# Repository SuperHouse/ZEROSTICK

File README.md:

"ZeroStick" Zero-Deflection Assistive Technology Joystick
==========================================================

ZeroStick is a joystick that uses strain gauges to measure force
applied to it, without the joystick needing to move. The joystick
"position" is determined from the force being applied to it, instead of
any physical deflection of the stick.

The term "position" is used here to signify the virtual position of the
joystick, even though it doesn't physically move. As more force is
applied, the virtual position of the joystick is considered to change.

This allows it to be used by people with a limited range of motion,
such as from Duchenne muscular dystrophy.

The sensitivity of the joystick can be adjusted in software by changing
the scaling of the values detected by the strain gauges.

The position value is measured as % deflection from the zero (central)
position, ie: from -100% to +100%. This is equivalent to full effort by
the user in each direction.

The force applied to the load cells is measured using a NAU7802 ADC
with an I2C interface. The input channels are split so that a single
ADC can read both the X and the Y axis load cells sequentially.

You can view more details at:

  http://www.superhouse.tv/zerostick

Hardware
--------
The "Hardware" directory contains the PCB design as an EAGLE project.
EAGLE PCB design software is available from Autodesk free for
non-commercial use.

Firmware
--------
The "Firmware" directory contains example firmware as an Arduino
project.

The example firmware has three output methods:

1. Mouse output. When enabled and plugged into a computer, the ZeroStick
will emulate a USB mouse. Buttons on the ZeroStick can also send left
and right click events.

2. Joystick output. When enabled and plugged into a computer, the
ZeroStick will emulate a USB game controller with a joystick.

3. I2C digital potentiometer output. External I2C digital potentiometers
can be connected, which can then emulate a simple analog joystick
when connected to another device such as a wheelchair. This allows the
ZeroStick to control wheelchairs that expect to have a normal joystick
attached.

Credits
-------
  * Jonathan Oxer <jon@oxer.com.au>
  * Chris Fryer <chris.fryer78@gmail.com>

License
-------
Copyright 2019-2021 SuperHouse Automation Pty Ltd  www.superhouse.tv  

The hardware portion of this project is licensed under the TAPR Open
Hardware License (www.tapr.org/OHL). The "license" folder within this
repository contains a copy of this license in plain text format.

The software portion of this project is licensed under the Simplified
BSD License. The "licence" folder within this project contains a
copy of this license in plain text format.

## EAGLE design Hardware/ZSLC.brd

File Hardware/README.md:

SuperButton Assistive Technology Button
=======================================
Copyright 2020 SuperHouse Automation Pty Ltd <www.superhouse.tv>  
Designed by Jonathan Oxer

Load-cell based button that can have the required activation force
adjusted in software, to tune it based on the needs of the user.

Features:

 * 1 x input connection for a load-cell based button
 * 1 x USB connection for power or to emulate an input device
 * 1 x switched output (either N.O. or N.C.) to control other devices
 * 128x32 OLED to show current force reading and activation threshold
 * Rotary encoder to adjust activation threshold
 * "Tare" button to reset zero point
 * Pulse stretching feature controlled by slide switch

More information is available at:

  http://www.superhouse.tv/sb

INSTALLATION
------------
The design is saved as an EAGLE project. EAGLE PCB design software is
available from www.cadsoftusa.com free for non-commercial use. To use
this project download it and place the directory containing these files
into the "eagle" directory on your computer. Then open EAGLE and
navigate to the project.

DISTRIBUTION
------------
The specific terms of distribution of this project are governed by the
license referenced below.

LICENSE
-------
Licensed under the TAPR Open Hardware License (www.tapr.org/OHL).
The "license" folder within this repository also contains a copy of
this license in plain text format.

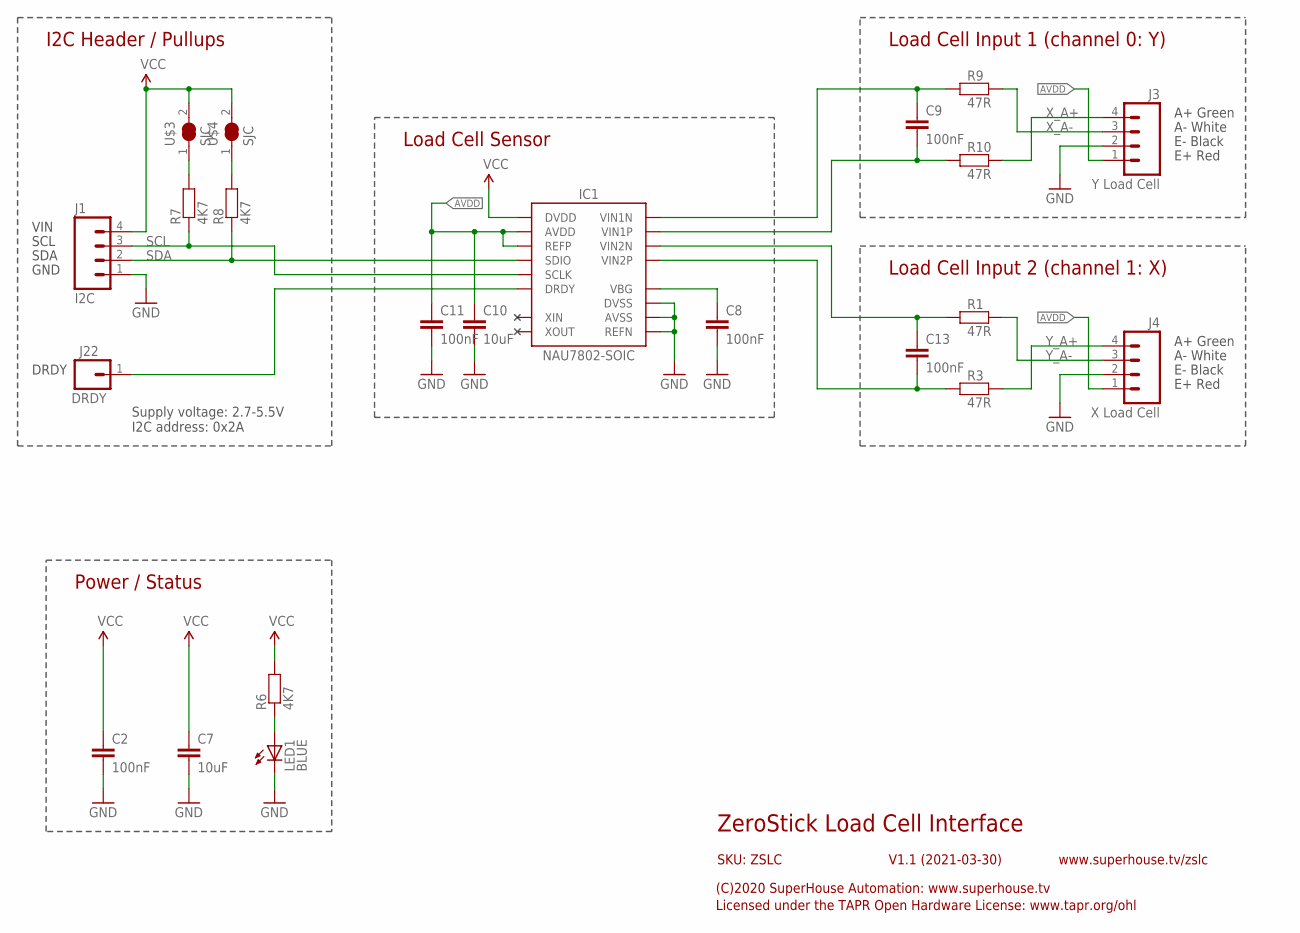
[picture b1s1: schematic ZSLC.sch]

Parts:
C2, C8, C9, C11, C13: 100nF; C0603
C7, C10: 10uF; C0805
IC1: NAU7802-SOIC; SO16
J1: I2C; 1X04
J3: Y Load Cell; 1X04-1.27-PLAIN
J4: X Load Cell; 1X04-1.27-PLAIN
J22: DRDY; 1X01
LED1: BLUE; LED-0603
R1, R3, R9, R10: 47R; R0603
R6, R7, R8: 4K7; R0603
U$3, U$4: SJC

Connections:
AVDD: C10.1, C11.1, IC1.1 (REFP), IC1.16 (AVDD), J3.1, J4.1
GND: C2.2, C7.2, C8.2, C10.2, C11.2, IC1.7 (REFN), IC1.8 (AVSS), IC1.9 (DVSS), J1.1, J3.2, J4.2, LED1.C
unnamed: IC1.12 (DRDY), J22.1
unnamed: C13.1, IC1.4 (VIN2N), R1.1
unnamed: C13.2, IC1.5 (VIN2P), R3.1
unnamed: LED1.A, R6.1
unnamed: C9.1, IC1.2 (VIN1N), R9.1
unnamed: C9.2, IC1.3 (VIN1P), R10.1
unnamed: C8.1, IC1.6 (VBG)
unnamed: R7.2, U$3.1
unnamed: R8.2, U$4.1
SCL: IC1.13 (SCLK), J1.3, R7.1
SDA: IC1.14 (SDIO), J1.2, R8.1
VCC: C2.1, C7.1, IC1.15 (DVDD), J1.4, R6.2, U$3.2, U$4.2
X_A+: J3.4, R10.2
X_A-: J3.3, R9.2
Y_A+: J4.4, R3.2
Y_A-: J4.3, R1.2

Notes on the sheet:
ZeroStick Load Cell Interface
V1.1 (2021-03-30)
SKU: ZSLC
(C)2020 SuperHouse Automation: www.superhouse.tv
Licensed under the TAPR Open Hardware License: www.tapr.org/ohl
www.superhouse.tv/zslc
Power / Status
Load Cell Input 1 (channel 0: Y)
Load Cell Input 2 (channel 1: X)
I2C Header / Pullups
E+ Red
E- Black
A- White
A+ Green
Supply voltage: 2.7-5.5V I2C address: 0x2A
Load Cell Sensor
VIN
SCL
SDA
GND
DRDY

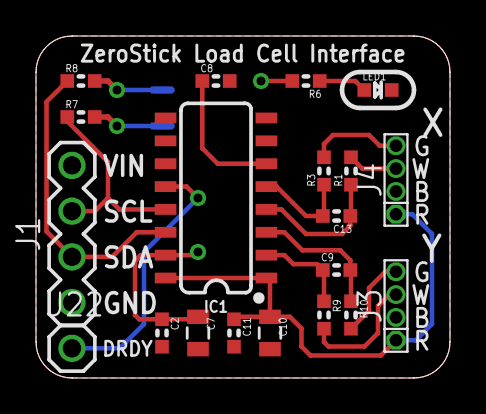
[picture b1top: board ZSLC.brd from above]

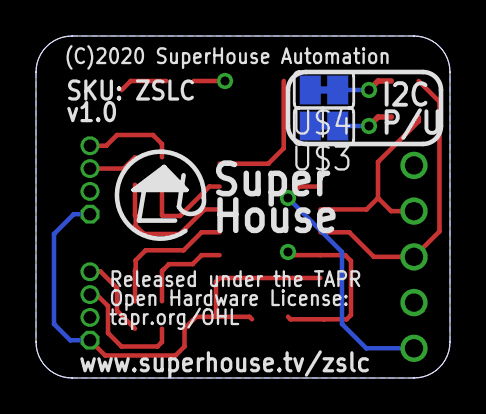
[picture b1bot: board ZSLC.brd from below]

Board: 2 copper layers, 23.0 x 19.0 mm, 22 parts (2 on the bottom side), 18 nets.

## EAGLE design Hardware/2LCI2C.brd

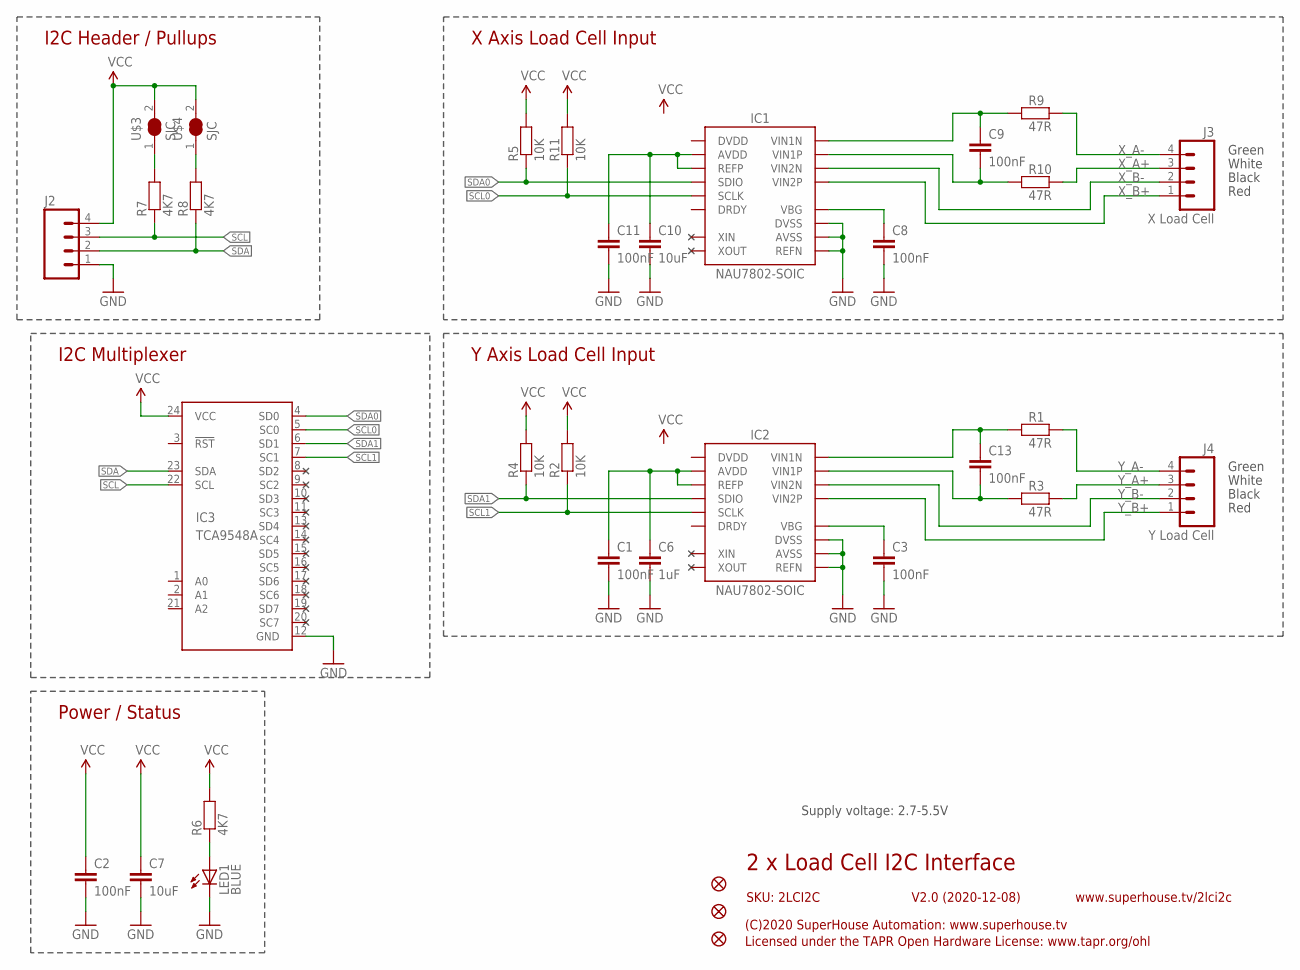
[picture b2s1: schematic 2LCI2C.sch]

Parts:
C1, C2, C3, C8, C9, C11, C13: 100nF; C0603
C6: 1uF; C0805
C7, C10: 10uF; C0805
IC1, IC2: NAU7802-SOIC; SO16
IC3: TCA9548A; TSSOP24
J2: M04-PLAIN; 1X04
J3: X Load Cell; 1X04-1.27-PLAIN
J4: Y Load Cell; 1X04-1.27-PLAIN
LED1: BLUE; LED-0603
R1, R3, R9, R10: 47R; R0603
R2, R4, R5, R11: 10K; R0603
R6, R7, R8: 4K7; R0603
U$3, U$4: SJC
U$5, U$10, U$11: FIDUCIAL1X2.5; FIDUCIAL-1X2.5

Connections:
GND: C1.2, C2.2, C3.2, C6.2, C7.2, C8.2, C10.2, C11.2, IC1.7 (REFN), IC1.8 (AVSS), IC1.9 (DVSS), IC2.7 (REFN), IC2.8 (AVSS), IC2.9 (DVSS), IC3.12 (GND), J2.1, LED1.C
unnamed: C3.1, IC2.6 (VBG)
unnamed: C13.1, IC2.2 (VIN1N), R1.1
unnamed: C1.1, C6.1, IC2.1 (REFP), IC2.16 (AVDD)
unnamed: C13.2, IC2.3 (VIN1P), R3.1
unnamed: LED1.A, R6.1
unnamed: C9.1, IC1.2 (VIN1N), R9.1
unnamed: C9.2, IC1.3 (VIN1P), R10.1
unnamed: C8.1, IC1.6 (VBG)
unnamed: C10.1, C11.1, IC1.1 (REFP), IC1.16 (AVDD)
unnamed: R7.2, U$3.1
unnamed: R8.2, U$4.1
SCL: IC3.22 (SCL), J2.3, R7.1
SCL0: IC1.13 (SCLK), IC3.5 (SC0), R11.1
SCL1: IC2.13 (SCLK), IC3.7 (SC1), R2.1
SDA: IC3.23 (SDA), J2.2, R8.1
SDA0: IC1.14 (SDIO), IC3.4 (SD0), R5.1
SDA1: IC2.14 (SDIO), IC3.6 (SD1), R4.1
VCC: C2.1, C7.1, IC3.24 (VCC), J2.4, R2.2, R4.2, R5.2, R6.2, R11.2, U$3.2, U$4.2
X_A+: J3.3, R10.2
X_A-: J3.4, R9.2
X_B+: IC1.5 (VIN2P), J3.1
X_B-: IC1.4 (VIN2N), J3.2
Y_A+: J4.3, R3.2
Y_A-: J4.4, R1.2
Y_B+: IC2.5 (VIN2P), J4.1
Y_B-: IC2.4 (VIN2N), J4.2

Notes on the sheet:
2 x Load Cell I2C Interface
V2.0 (2020-12-08)
SKU: 2LCI2C
(C)2020 SuperHouse Automation: www.superhouse.tv
Licensed under the TAPR Open Hardware License: www.tapr.org/ohl
www.superhouse.tv/2lci2c
Power / Status
X Axis Load Cell Input
Y Axis Load Cell Input
I2C Header / Pullups
I2C Multiplexer
Red
Black
White
Green
Supply voltage: 2.7-5.5V

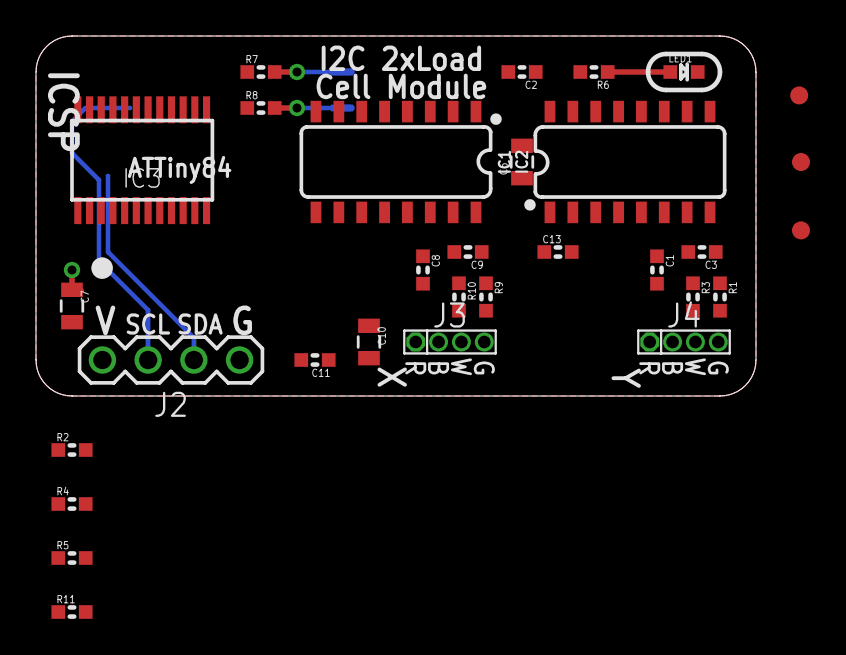
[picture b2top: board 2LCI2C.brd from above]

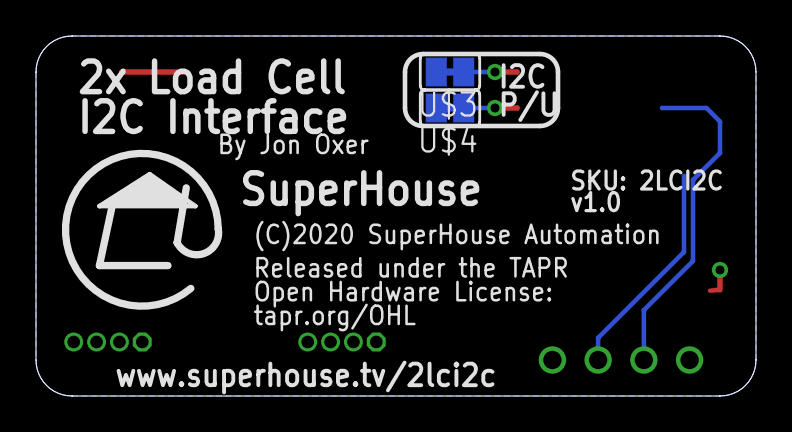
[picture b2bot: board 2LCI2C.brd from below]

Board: 2 copper layers, 40.0 x 20.0 mm, 33 parts (2 on the bottom side), 27 nets.

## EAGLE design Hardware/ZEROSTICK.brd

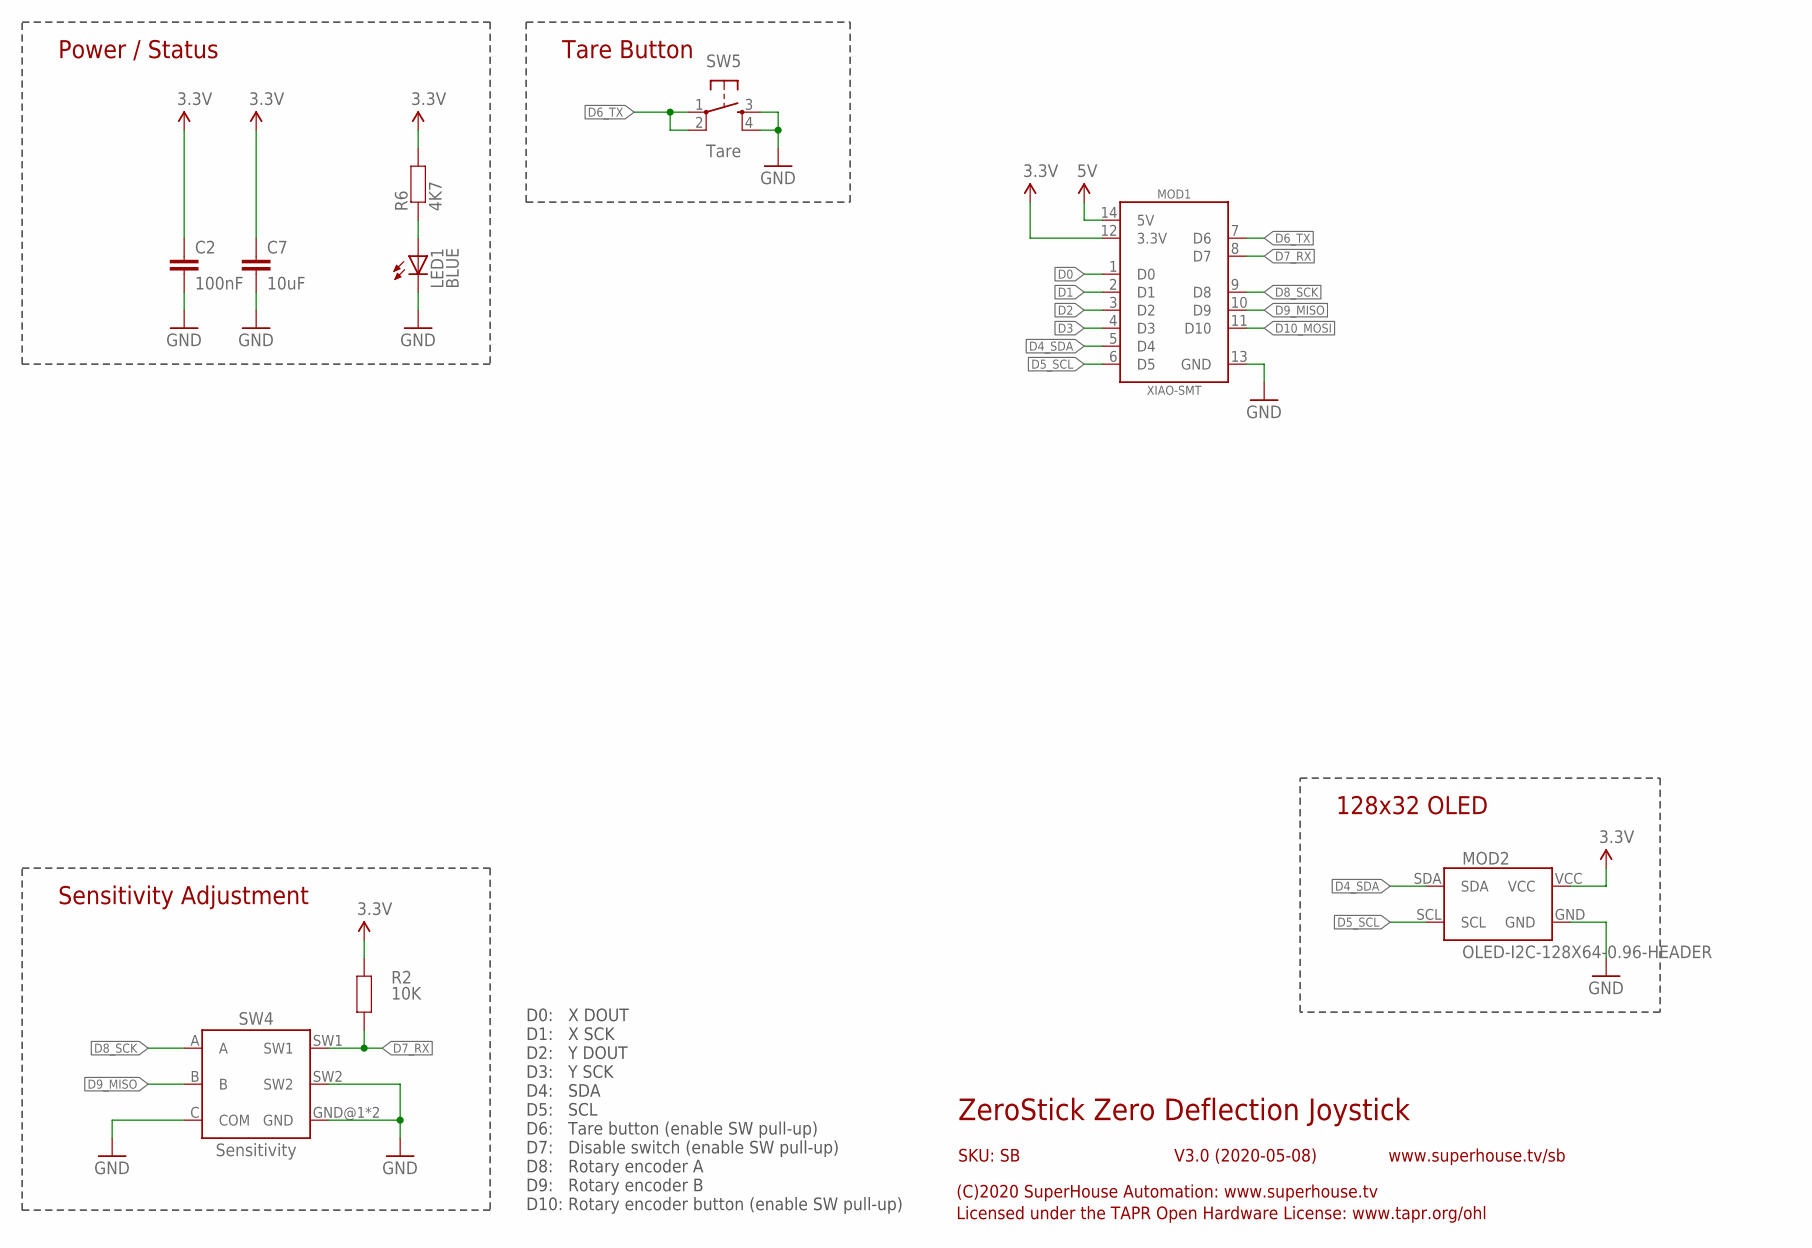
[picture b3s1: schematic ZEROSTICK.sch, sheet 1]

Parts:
C2: 100nF; C0603
C7: 10uF; C0805
LED1: BLUE; LED-0603
MOD1: XIAO-SMT
MOD2: OLED-I2C-128X64-0.96-HEADER; OLED-128X64-0.96-HEADER
R2: 10K; R0603
R6: 4K7; R0603
SW4: Sensitivity; PEC12R
SW5: Tare; TACTILE-PTH-4.5MM

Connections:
3.3V: C2.1, C7.1, MOD1.12 (3.3V), MOD2.VCC, R2.2, R6.2; also elsewhere on the board
5V: MOD1.14 (5V)
D0: MOD1.1 (D0); also elsewhere on the board
D1: MOD1.2 (D1); also elsewhere on the board
D2: MOD1.3 (D2); also elsewhere on the board
D3: MOD1.4 (D3); also elsewhere on the board
D4_SDA: MOD1.5 (D4), MOD2.SDA
D5_SCL: MOD1.6 (D5), MOD2.SCL
D6_TX: MOD1.7 (D6), SW5.1, SW5.2
D7_RX: MOD1.8 (D7), R2.1, SW4.SW1
D8_SCK: MOD1.9 (D8), SW4.A
D9_MISO: MOD1.10 (D9), SW4.B
D10_MOSI: MOD1.11 (D10)
GND: C2.2, C7.2, LED1.C, MOD1.13 (GND), MOD2.GND, SW4.C (COM), SW4.GND@1 (GND), SW4.GND@2 (GND), SW4.SW2, SW5.3, SW5.4; also elsewhere on the board
unnamed: LED1.A, R6.1

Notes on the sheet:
Tare Button
ZeroStick Zero Deflection Joystick
V3.0 (2020-05-08)
SKU: SB
(C)2020 SuperHouse Automation: www.superhouse.tv
Licensed under the TAPR Open Hardware License: www.tapr.org/ohl
www.superhouse.tv/sb
Power / Status
Sensitivity Adjustment
128x32 OLED
D0: X DOUT D1: X SCK D2: Y DOUT D3: Y SCK D4: SDA D5: SCL D6: Tare button (enable SW pull-up) D7: Disable switch (enable SW pull-up) D8: Rotary encoder A D9: Rotary encoder B D10: Rotary encoder button (enable SW pull-up)

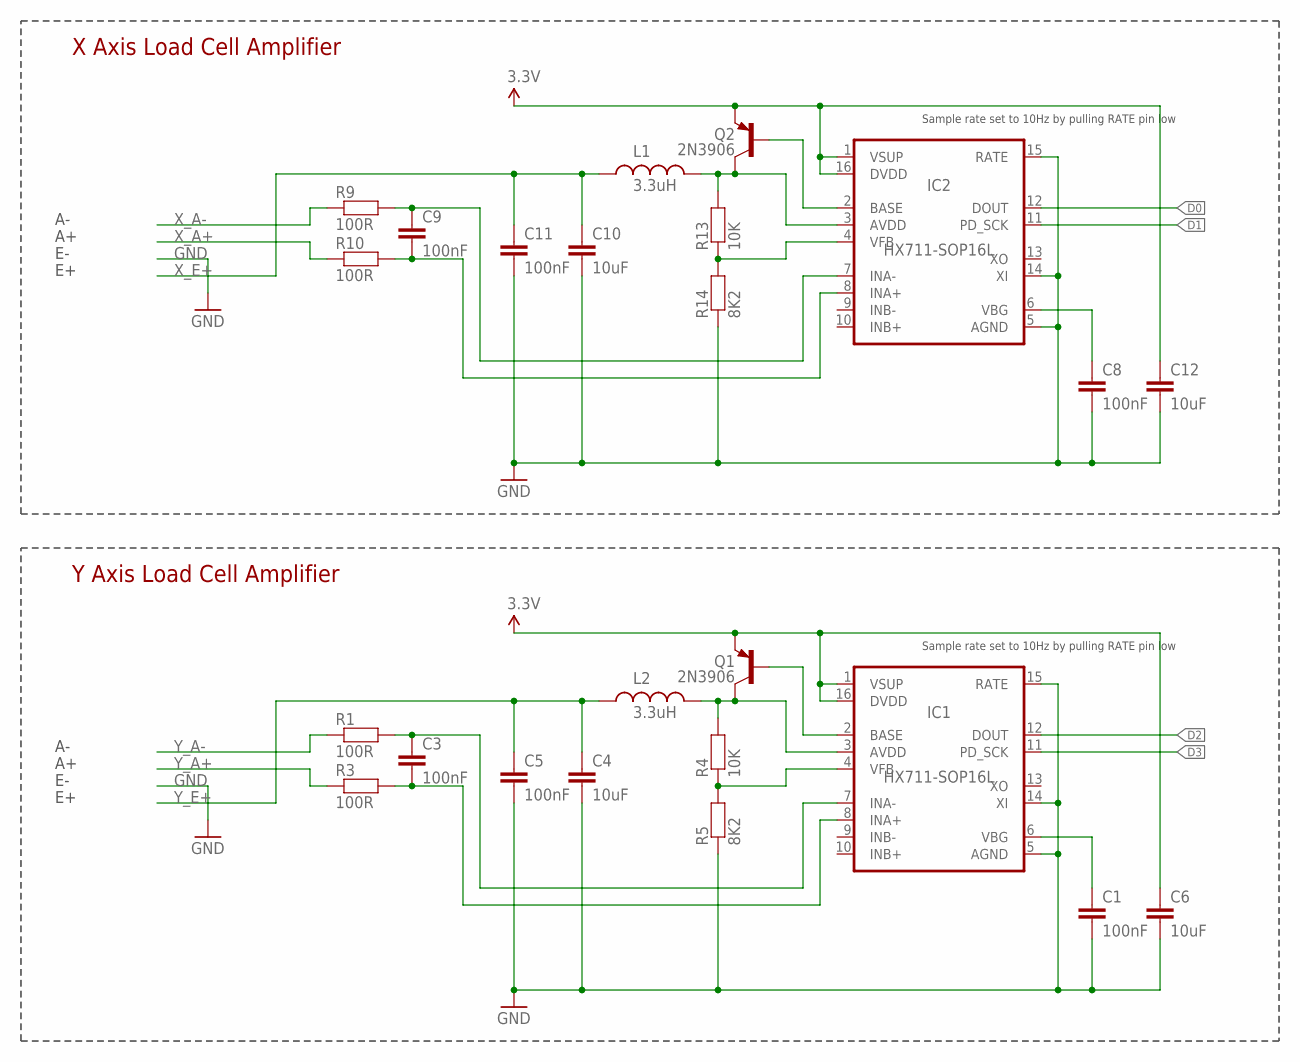
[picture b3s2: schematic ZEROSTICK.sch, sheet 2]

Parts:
C1, C3, C5, C8, C9, C11: 100nF; C0603
C4, C6, C10, C12: 10uF; C0805
IC1, IC2: HX711-SOP16L; SOP16-L
L1, L2: 3.3uH; L0603
Q1, Q2: 2N3906; SOT23-BEC
R1, R3, R9, R10: 100R; R0603
R4, R13: 10K; R0603
R5, R14: 8K2; R0603

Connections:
3.3V: C6.1, C12.1, IC1.1 (VSUP), IC1.16 (DVDD), IC2.1 (VSUP), IC2.16 (DVDD), Q1.E, Q2.E; also elsewhere on the board
D0: IC2.12 (DOUT); also elsewhere on the board
D1: IC2.11 (PD_SCK); also elsewhere on the board
D2: IC1.12 (DOUT); also elsewhere on the board
D3: IC1.11 (PD_SCK); also elsewhere on the board
GND: C1.2, C4.2, C5.2, C6.2, C8.2, C10.2, C11.2, C12.2, IC1.5 (AGND), IC1.14 (XI), IC1.15 (RATE), IC2.5 (AGND), IC2.14 (XI), IC2.15 (RATE), R5.1, R14.1; also elsewhere on the board
unnamed: C3.1, IC1.7 (INA-), R1.2
unnamed: C3.2, IC1.8 (INA+), R3.2
unnamed: C1.1, IC1.6 (VBG)
unnamed: IC1.2 (BASE), Q1.B
unnamed: IC1.4 (VFB), R4.1, R5.2
unnamed: IC1.3 (AVDD), L2.2, Q1.C, R4.2
unnamed: C9.1, IC2.7 (INA-), R9.2
unnamed: C9.2, IC2.8 (INA+), R10.2
unnamed: IC2.3 (AVDD), L1.2, Q2.C, R13.2
unnamed: C8.1, IC2.6 (VBG)
unnamed: IC2.2 (BASE), Q2.B
unnamed: IC2.4 (VFB), R13.1, R14.2
XO: IC1.13 (XO), IC2.13 (XO)
X_A+: R10.1
X_A-: R9.1
X_E+: C10.1, C11.1, L1.1
Y_A+: R3.1
Y_A-: R1.1
Y_E+: C4.1, C5.1, L2.1

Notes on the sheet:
X Axis Load Cell Amplifier
Sample rate set to 10Hz by pulling RATE pin low
Y Axis Load Cell Amplifier

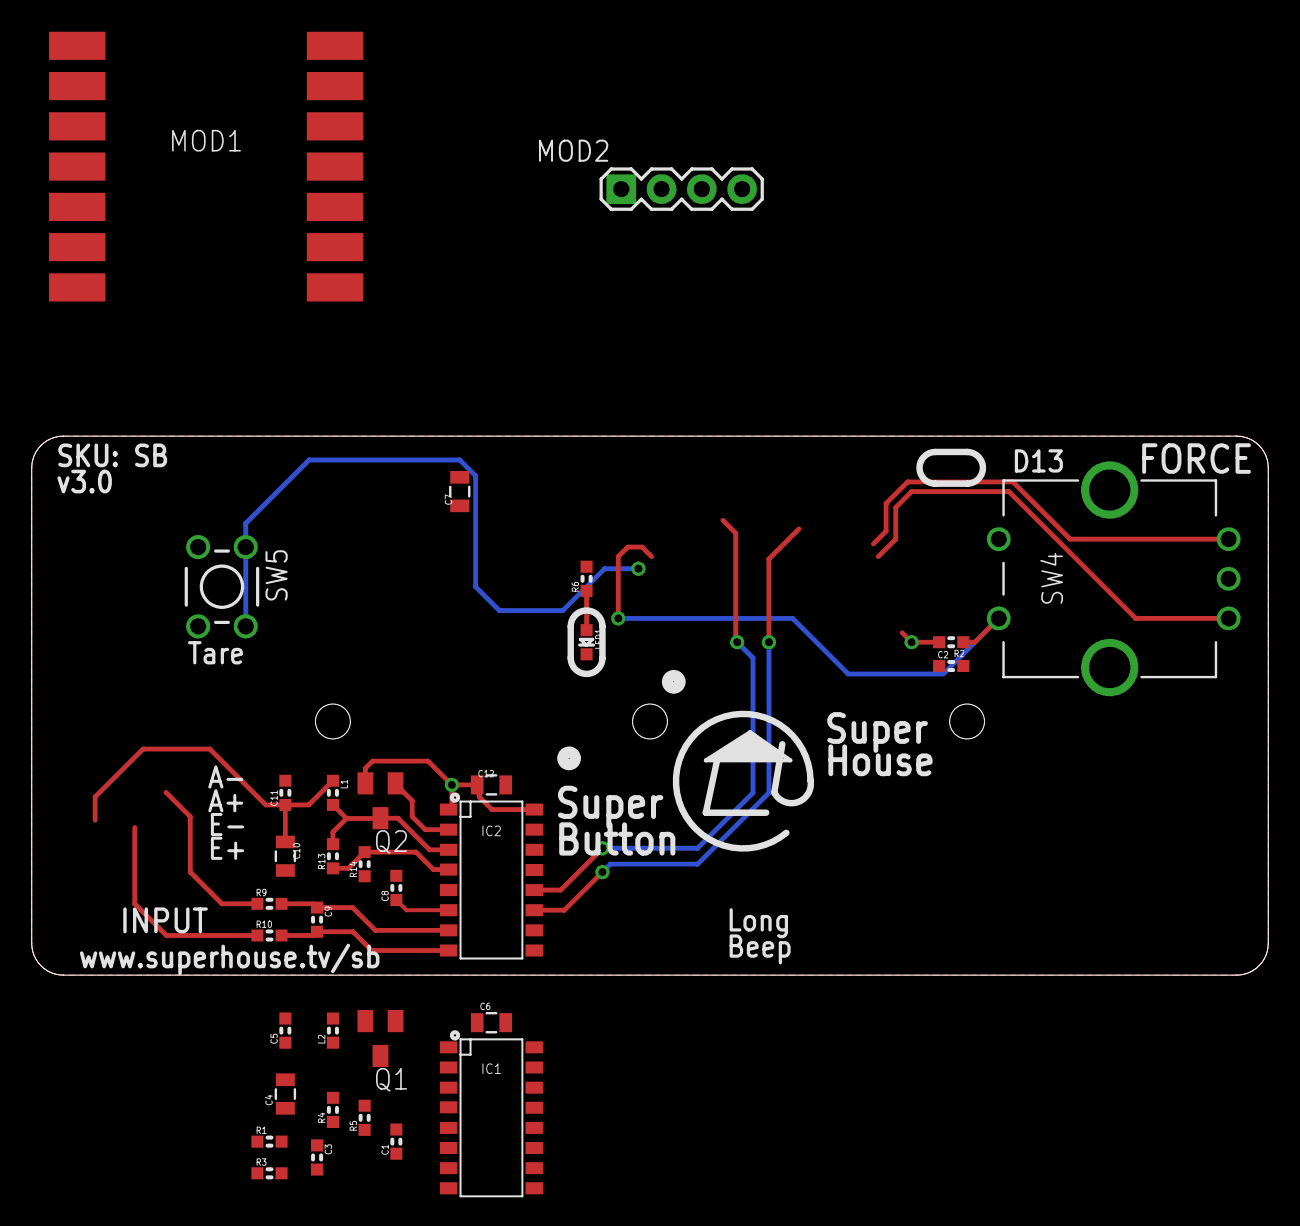
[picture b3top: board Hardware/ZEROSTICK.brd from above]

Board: 2 copper layers, 78.0 x 34.0 mm, 33 parts (0 on the bottom side), 28 nets.

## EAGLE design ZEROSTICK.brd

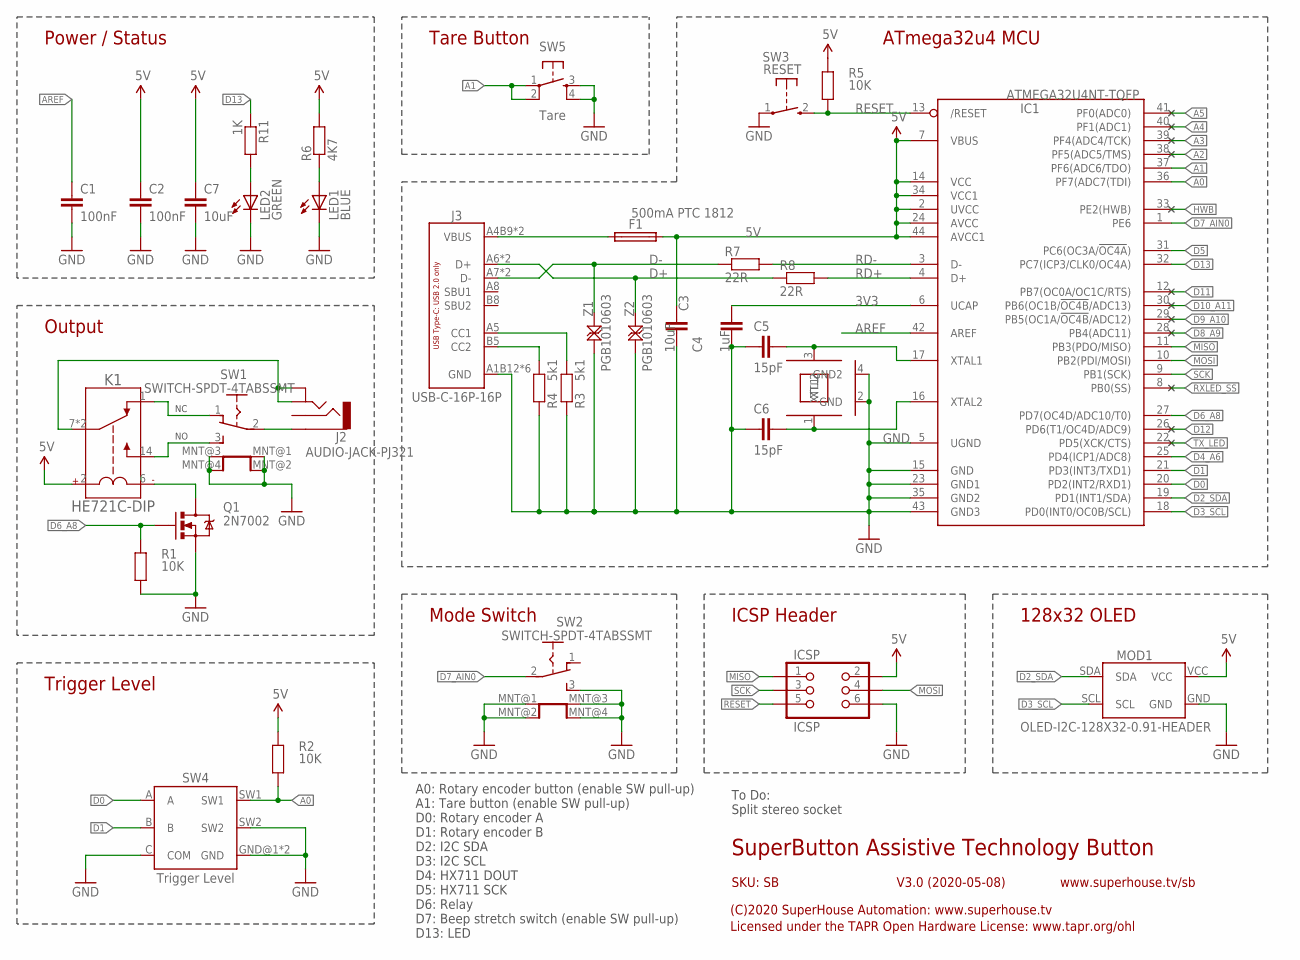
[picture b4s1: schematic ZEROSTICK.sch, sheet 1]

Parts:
C1, C2: 100nF; C0603
C3, C7: 10uF; C0805
C4: 1uF; C0603
C5, C6: 15pF; C0603
F1: 500mA PTC 1812; 1812
IC1: ATMEGA32U4NT-TQFP; TQFP44
ICSP: ICSP; 2X03-ICSP
J2: AUDIO-JACK-PJ321
J3: USB-C-16P-16P; USB-C-16P
K1: HE721C-DIP; HE721
LED1: BLUE; LED-0603
LED2: GREEN; LED-0603
MOD1: OLED-I2C-128X32-0.91-HEADER; OLED-128X32-0.91-HEADER
Q1: 2N7002; SOT23-3
R1, R2, R5: 10K; R0603
R3, R4: 5k1; R0603
R6: 4K7; R0603
R7, R8: 22R; R0603
R11: 1K; R0603
SW1, SW2: SWITCH-SPDT-4TABSSMT; MK-12C02
SW3: RESET; TACTILE_SMT_3X4X2
SW4: Trigger Level; PEC12R
SW5: Tare; TACTILE-PTH-4.5MM
XTL1: 16MHz; CRYSTAL-SMD-3X2
Z1, Z2: PGB1010603; TVS0603

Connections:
3V3: C4.2, IC1.6 (UCAP)
5V: C2.1, C3.1, C7.1, F1.2, IC1.2 (UVCC), IC1.7 (VBUS), IC1.14 (VCC), IC1.24 (AVCC), IC1.34 (VCC1), IC1.44 (AVCC1), ICSP.2, K1.2 (COIL+), MOD1.VCC, R2.2, R5.2, R6.2; also elsewhere on the board
A0: IC1.36 (PF7(ADC7(TDI)), R2.1, SW4.SW1
A1: IC1.37 (PF6(ADC6/TDO)), SW5.1, SW5.2
A2: IC1.38 (PF5(ADC5/TMS))
A3: IC1.39 (PF4(ADC4/TCK))
A4: IC1.40 (PF1(ADC1))
A5: IC1.41 (PF0(ADC0))
AREF: C1.1, IC1.42 (AREF)
D0: IC1.20 (PD2(INT2/RXD1)), SW4.A
D1: IC1.21 (PD3(INT3/TXD1)), SW4.B
D2_SDA: IC1.19 (PD1(INT1/SDA)), MOD1.SDA
D3_SCL: IC1.18 (PD0(INT0/OC0B/SCL)), MOD1.SCL
D4_A6: IC1.25 (PD4(ICP1/ADC8)); also elsewhere on the board
D5: IC1.31 (PC6(OC3A/!OC4A!)); also elsewhere on the board
D6_A8: IC1.27 (PD7(OC4D/ADC10/T0)), Q1.1 (G), R1.2
D7_AIN0: IC1.1 (PE6), SW2.2 (COM)
D8_A9: IC1.28 (PB4(ADC11))
D9_A10: IC1.29 (PB5(OC1A/!OC4B!/ADC12))
D10_A11: IC1.30 (PB6(OC1B/!OC4B!/ADC13))
D11: IC1.12 (PB7(OC0A/OC1C/RTS))
D12: IC1.26 (PD6(T1/OC4D/ADC9))
D13: IC1.32 (PC7(ICP3/CLK0/OC4A)), R11.1
D+: J3.A6 (D+), J3.B6 (D+), R8.1, Z2.2
D-: J3.A7 (D-), J3.B7 (D-), R7.1, Z1.2
GND: C1.2, C2.2, C3.2, C4.1, C5.1, C6.1, C7.2, IC1.5 (UGND), IC1.15 (GND), IC1.23 (GND1), IC1.35 (GND2), IC1.43 (GND3), ICSP.6, J3.A1B12 (GND), J3.A12B1 (GND), J3.FIX1 (GND), J3.FIX2 (GND), J3.FIX3 (GND), J3.FIX4 (GND), LED1.C, LED2.C, MOD1.GND, Q1.2 (S), R1.1, R3.1, R4.1, SW1.MNT@1 (MNT), SW1.MNT@2 (MNT), SW1.MNT@3 (MNT), SW1.MNT@4 (MNT), SW2.3 (B), SW2.MNT@1 (MNT), SW2.MNT@2 (MNT), SW2.MNT@3 (MNT), SW2.MNT@4 (MNT), SW3.1, SW4.C (COM), SW4.GND@1 (GND), SW4.GND@2 (GND), SW4.SW2, SW5.3, SW5.4, XTL1.2 (GND), XTL1.4 (GND2), Z1.1, Z2.1; also elsewhere on the board
HWB: IC1.33 (PE2(HWB))
MISO: IC1.11 (PB3(PDO/MISO)), ICSP.1
MOSI: IC1.10 (PB2(PDI/MOSI)), ICSP.4
unnamed: LED2.A, R11.2
unnamed: K1.6 (COIL-), Q1.3 (D)
unnamed: K1.14 (NO), SW1.3 (B)
unnamed: LED1.A, R6.1
unnamed: K1.1 (NC), SW1.1 (A)
unnamed: J2.4A, J2.4B, K1.7 (COM), K1.8 (COM)
unnamed: J2.3, SW1.2 (COM)
unnamed: J3.B5 (CC2), R4.2
unnamed: C5.2, IC1.17 (XTAL1), XTL1.3 (XTL2)
unnamed: C6.2, IC1.16 (XTAL2), XTL1.1 (XTL1)
unnamed: J3.A5 (CC1), R3.2
RD+: IC1.4 (D+), R8.2
RD-: IC1.3 (D-), R7.2
RESET: IC1.13 (/RESET), ICSP.5, R5.1, SW3.2 (S)
RXLED_SS: IC1.8 (PB0(SS))
SCK: IC1.9 (PB1(SCK)), ICSP.3
TX_LED: IC1.22 (PD5(XCK/CTS))
USB+: F1.1, J3.A4B9 (VBUS), J3.A9B4 (VBUS)

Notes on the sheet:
ICSP Header
Tare Button
SuperButton Assistive Technology Button
V3.0 (2020-05-08)
SKU: SB
(C)2020 SuperHouse Automation: www.superhouse.tv
Licensed under the TAPR Open Hardware License: www.tapr.org/ohl
www.superhouse.tv/sb
Power / Status
Output
Trigger Level
128x32 OLED
A0: Rotary encoder button (enable SW pull-up) A1: Tare button (enable SW pull-up) D0: Rotary encoder A D1: Rotary encoder B D2: I2C SDA D3: I2C SCL D4: HX711 DOUT D5: HX711 SCK D6: Relay D7: Beep stretch switch (enable SW pull-up) D13: LED
To Do: Split stereo socket
Mode Switch
ATmega32u4 MCU

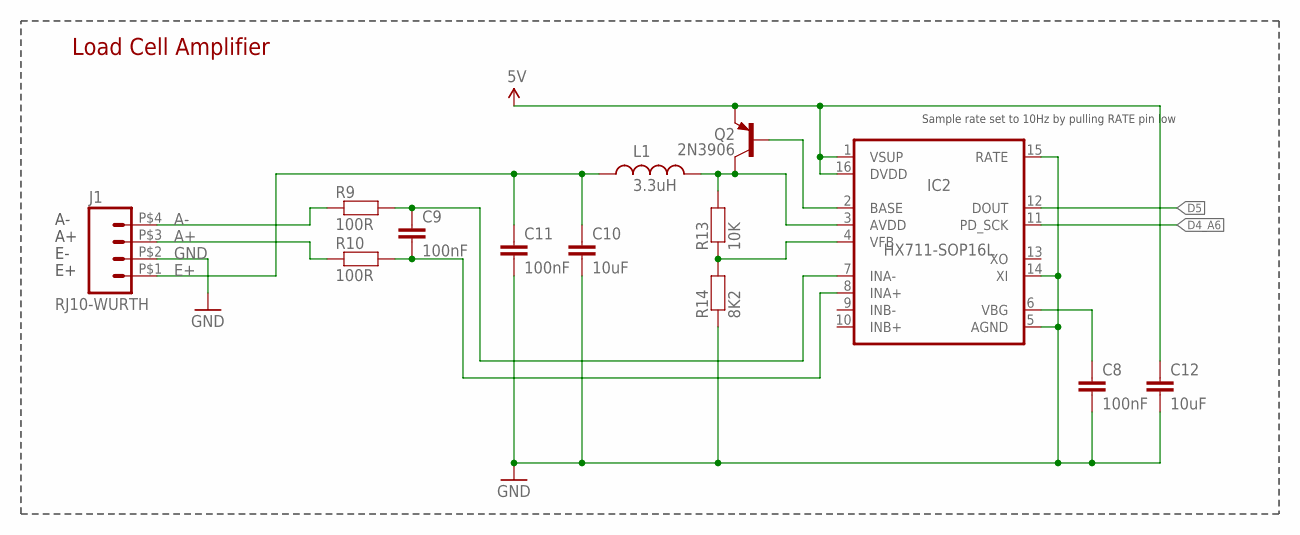
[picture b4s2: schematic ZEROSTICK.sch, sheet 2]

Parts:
C8, C9, C11: 100nF; C0603
C10, C12: 10uF; C0805
IC2: HX711-SOP16L; SOP16-L
J1: RJ10-WURTH; RJ10
L1: 3.3uH; L0603
Q2: 2N3906; SOT23-BEC
R9, R10: 100R; R0603
R13: 10K; R0603
R14: 8K2; R0603

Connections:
5V: C12.1, IC2.1 (VSUP), IC2.16 (DVDD), Q2.E; also elsewhere on the board
A+: J1.P$3 (3), R10.1
A-: J1.P$4 (4), R9.1
D4_A6: IC2.11 (PD_SCK); also elsewhere on the board
D5: IC2.12 (DOUT); also elsewhere on the board
E+: C10.1, C11.1, J1.P$1 (1), L1.1
GND: C8.2, C10.2, C11.2, C12.2, IC2.5 (AGND), IC2.14 (XI), IC2.15 (RATE), J1.P$2 (2), R14.1; also elsewhere on the board
unnamed: C9.1, IC2.7 (INA-), R9.2
unnamed: C9.2, IC2.8 (INA+), R10.2
unnamed: IC2.3 (AVDD), L1.2, Q2.C, R13.2
unnamed: C8.1, IC2.6 (VBG)
unnamed: IC2.2 (BASE), Q2.B
unnamed: IC2.4 (VFB), R13.1, R14.2
XO: IC2.13 (XO)

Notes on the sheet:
Load Cell Amplifier
Sample rate set to 10Hz by pulling RATE pin low

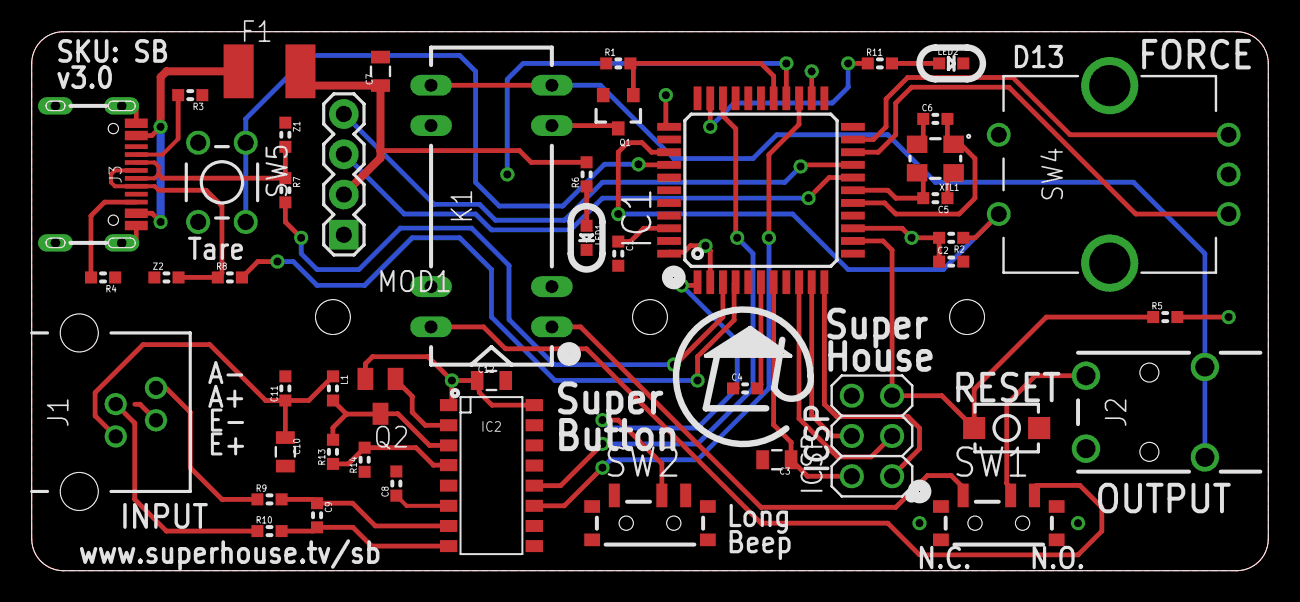
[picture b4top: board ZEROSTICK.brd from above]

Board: 2 copper layers, 78.0 x 34.0 mm, 47 parts (0 on the bottom side), 44 nets.

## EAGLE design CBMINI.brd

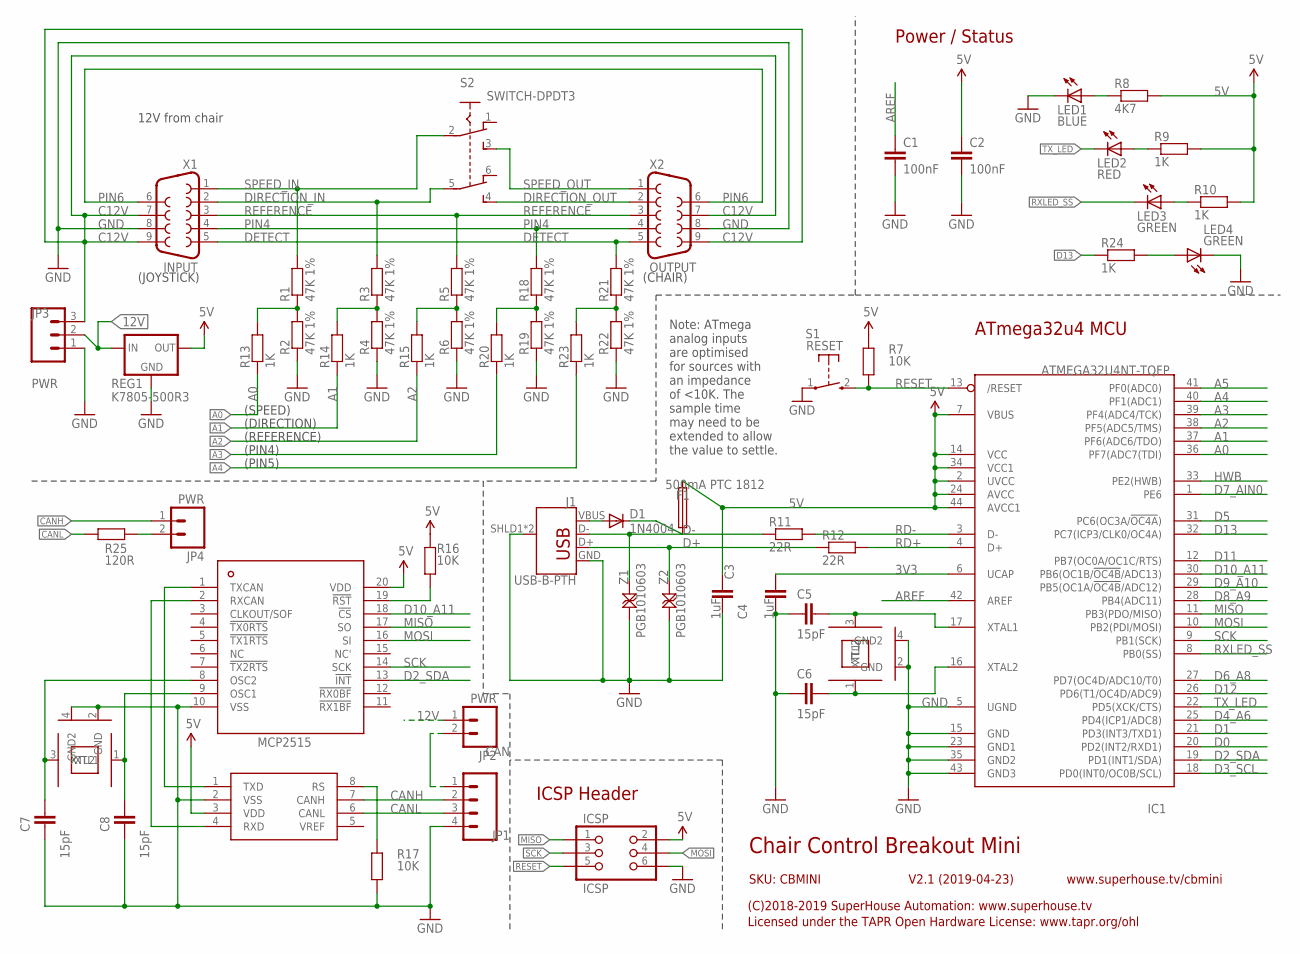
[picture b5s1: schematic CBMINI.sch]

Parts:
C1, C2: 100nF; C0603
C3, C4: 1uF; C0603
C5, C6, C7, C8: 15pF; C0603
D1: 1N4004; SMA-DIODE
F1: 500mA PTC 1812; 1812
IC1: ATMEGA32U4NT-TQFP; TQFP44
IC2: MCP2515; TSSOP20
IC3: MCP2551; SO08
ICSP: ICSP; 2X03-ICSP
J1: USB-B-PTH
JP1: CAN; 1X04-P
JP2, JP4: PWR; 1X02-P
JP3: PWR; 1X03-P
LED1: BLUE; LED-0603
LED2: RED; LED-0603
LED3, LED4: GREEN; LED-0603
R1, R2, R3, R4, R5, R6, R18, R19, R21, R22: 47K 1%; R0603
R7, R16, R17: 10K; R0603
R8: 4K7; R0603
R9, R10, R13, R14, R15, R20, R23, R24: 1K; R0603
R11, R12: 22R; R0603
R25: 120R; R0603
REG1: K7805-500R3; K78XX-500R3
S1: RESET; TACTILE_SMT_3X4X2
S2: SWITCH-DPDT3; 7201SD9AV2BE
X1: INPUT; DB9_MALE
X2: OUTPUT; DB9
XTL1, XTL2: 16MHz; CRYSTAL-SMD-3X2
Z1, Z2: PGB1010603; TVS0603

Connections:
3V3: C4.2, IC1.6 (UCAP)
5V: C2.1, C3.1, F1.2, IC1.2 (UVCC), IC1.7 (VBUS), IC1.14 (VCC), IC1.24 (AVCC), IC1.34 (VCC1), IC1.44 (AVCC1), IC2.20 (VDD), IC3.3 (VDD), ICSP.2, R7.2, R8.2, R9.2, R10.2, R16.2, REG1.3 (OUT)
12V: JP2.1, JP3.2, REG1.1 (IN)
A0: IC1.36 (PF7(ADC7(TDI)), R13.1
A1: IC1.37 (PF6(ADC6/TDO)), R14.1
A2: IC1.38 (PF5(ADC5/TMS)), R15.1
A3: IC1.39 (PF4(ADC4/TCK)), R20.1
A4: IC1.40 (PF1(ADC1)), R23.1
A5: IC1.41 (PF0(ADC0))
AREF: C1.1, IC1.42 (AREF)
C12V: JP3.3, X1.7, X1.9, X2.7, X2.9
CANH: IC3.7 (CANH), JP1.2, JP4.1
CANL: IC3.6 (CANL), JP1.3, R25.1
D0: IC1.20 (PD2(INT2/RXD1))
D1: IC1.21 (PD3(INT3/TXD1))
D2_SDA: IC1.19 (PD1(INT1/SDA)), IC2.13 (!INT)
D3_SCL: IC1.18 (PD0(INT0/OC0B/SCL))
D4_A6: IC1.25 (PD4(ICP1/ADC8))
D5: IC1.31 (PC6(OC3A/!OC4A!))
D6_A8: IC1.27 (PD7(OC4D/ADC10/T0))
D7_AIN0: IC1.1 (PE6)
D8_A9: IC1.28 (PB4(ADC11))
D9_A10: IC1.29 (PB5(OC1A/!OC4B!/ADC12))
D10_A11: IC1.30 (PB6(OC1B/!OC4B!/ADC13)), IC2.18 (!CS)
D11: IC1.12 (PB7(OC0A/OC1C/RTS))
D12: IC1.26 (PD6(T1/OC4D/ADC9))
D13: IC1.32 (PC7(ICP3/CLK0/OC4A)), R24.1
D+: J1.D+, R12.1, Z2.2
D-: J1.D-, R11.1, Z1.2
DETECT: R21.2, X1.5, X2.5
DIRECTION_IN: R3.2, S2.5, X1.2
DIRECTION_OUT: S2.4, X2.2
GND: C1.2, C2.2, C3.2, C4.1, C5.1, C6.1, C7.1, C8.1, IC1.5 (UGND), IC1.15 (GND), IC1.23 (GND1), IC1.35 (GND2), IC1.43 (GND3), IC2.10 (VSS), IC3.2 (VSS), ICSP.6, J1.GND, J1.SHLD1 (SHIELD), J1.SHLD2 (SHIELD), JP1.4, JP3.1, LED1.C, LED4.C, R2.1, R4.1, R6.1, R17.1, R19.1, R22.1, REG1.2 (GND), S1.1, X1.8, X2.8, XTL1.2 (GND), XTL1.4 (GND2), XTL2.2 (GND), XTL2.4 (GND2), Z1.1, Z2.1
HWB: IC1.33 (PE2(HWB))
MISO: IC1.11 (PB3(PDO/MISO)), IC2.17 (SO), ICSP.1
MOSI: IC1.10 (PB2(PDI/MOSI)), IC2.16 (SI), ICSP.4
unnamed: LED4.A, R24.2
unnamed: R1.1, R2.2, R13.2
unnamed: R3.1, R4.2, R14.2
unnamed: R5.1, R6.2, R15.2
unnamed: LED1.A, R8.1
unnamed: LED2.A, R9.1
unnamed: LED3.A, R10.1
unnamed: IC2.1 (TXCAN), IC3.1 (TXD)
unnamed: IC2.19 (!RST), R16.1
unnamed: C5.2, IC1.17 (XTAL1), XTL1.3 (XTL2)
unnamed: C6.2, IC1.16 (XTAL2), XTL1.1 (XTL1)
unnamed: IC2.2 (RXCAN), IC3.4 (RXD)
unnamed: C8.2, IC2.9 (OSC1), XTL2.1 (XTL1)
unnamed: JP1.1, JP2.2
unnamed: IC3.8 (RS), R17.2
unnamed: D1.C, F1.1
unnamed: C7.2, IC2.8 (OSC2), XTL2.3 (XTL2)
unnamed: R18.1, R19.2, R20.2
unnamed: JP4.2, R25.2
unnamed: R21.1, R22.2, R23.2
PIN4: R18.2, X1.4, X2.4
PIN6: X1.6, X2.6
RD+: IC1.4 (D+), R12.2
RD-: IC1.3 (D-), R11.2
REFERENCE: R5.2, X1.3, X2.3
RESET: IC1.13 (/RESET), ICSP.5, R7.1, S1.2 (S)
RXLED_SS: IC1.8 (PB0(SS)), LED3.C
SCK: IC1.9 (PB1(SCK)), IC2.14 (SCK), ICSP.3
SPEED_IN: R1.2, S2.2, X1.1
SPEED_OUT: S2.3, X2.1
TX_LED: IC1.22 (PD5(XCK/CTS)), LED2.C
USB+: D1.A, J1.VBUS

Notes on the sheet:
(JOYSTICK)
(CHAIR)
Note: ATmega analog inputs are optimised for sources with an impedance of <10K. The sample time may need to be extended to allow the value to settle.
(SPEED)
(DIRECTION)
(REFERENCE)
ICSP Header
ATmega32u4 MCU
Chair Control Breakout Mini
V2.1 (2019-04-23)
SKU: CBMINI
(C)2018-2019 SuperHouse Automation: www.superhouse.tv
Licensed under the TAPR Open Hardware License: www.tapr.org/ohl
www.superhouse.tv/cbmini
Power / Status
12V from chair
(PIN4)
(PIN5)

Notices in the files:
CBMINI.brd:
(C)2018-2019 SuperHouse Automation P/L
CBMINICONN.brd:
(C)2018 SuperHouse Automation P/L
Hardware/ZEROSTICK.brd:
(C)2020 SuperHouse Automation P/L
parts and their libraries:
SparkFun-Connectors: Licensing: CC v3.0 Share-Alike You are welcome to use this library for commercial purposes.
